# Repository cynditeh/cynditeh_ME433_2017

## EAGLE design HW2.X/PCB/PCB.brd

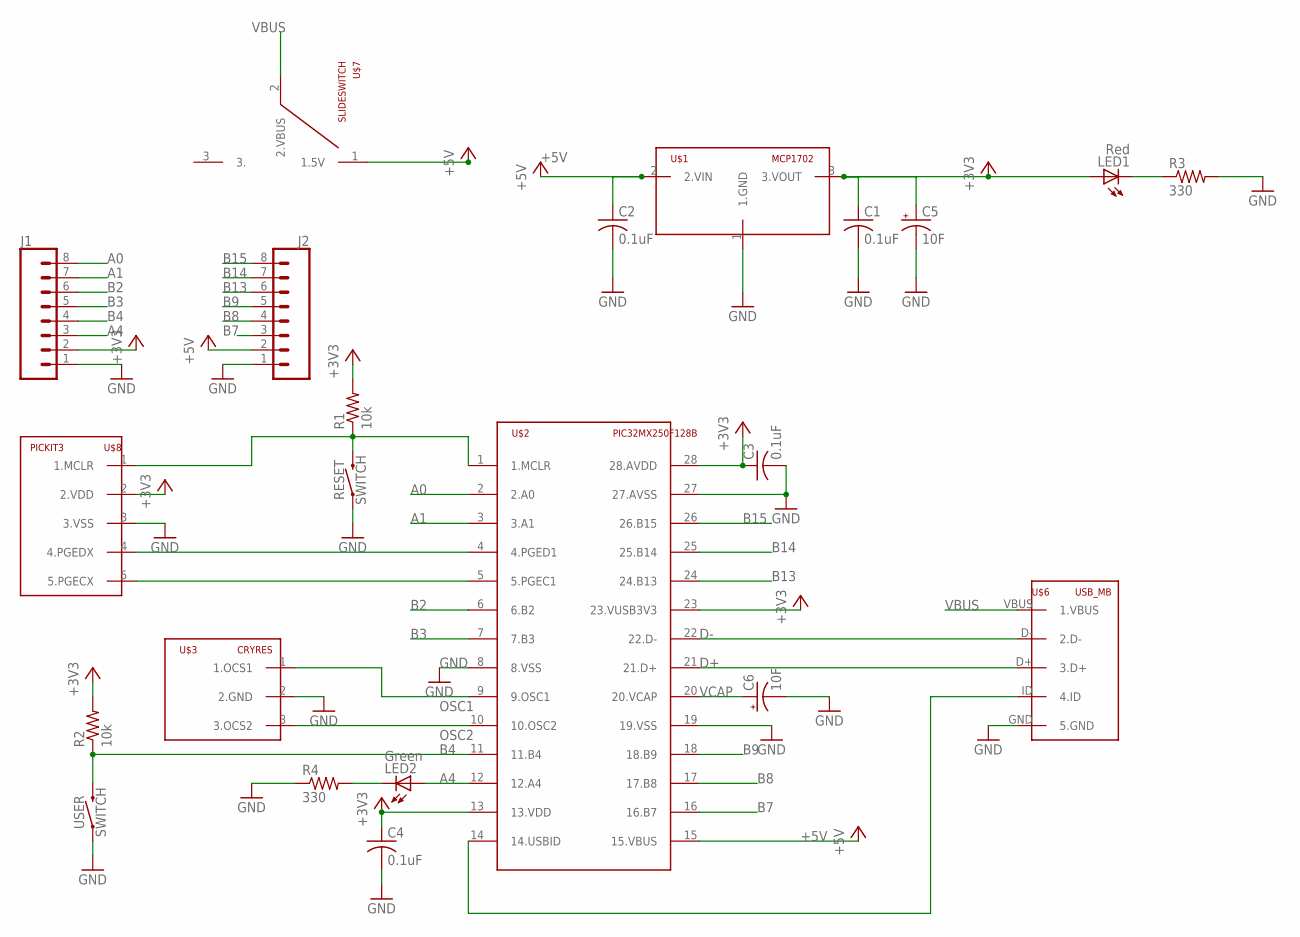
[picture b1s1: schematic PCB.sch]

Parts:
C1, C2, C3, C4: 0.1uF; C025-025X050
C5, C6: 10F; E5-5
J1, J2: CONN_08"; 1X08
LED1: Red; LED3MM
LED2: Green; LED3MM
R1, R2: 10k; 0207/10
R3, R4: 330; 0207/10
RESET: SWITCH
U$1: MCP1702; TO92
U$2: PIC32MX250F128B; DIL28-3
U$3: CRYRES; CRYSTAL
U$6: USB_MB; USB-MB-H
U$7: SLIDESWITCH
U$8: PICKIT3; 1X05
USER: SWITCH

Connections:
+3V3: C1.1, C3.1, C4.1, C5.+, J1.2, LED1.A, R1.2, R2.2, U$1.3 (3.VOUT), U$2.13 (13.VDD), U$2.23 (23.VUSB3V3), U$2.28 (28.AVDD), U$8.2 (2.VDD)
+5V: C2.1, J2.2, U$1.2 (2.VIN), U$2.15 (15.VBUS), U$7.1 (1.5V)
A0: J1.8, U$2.2 (2.A0)
A1: J1.7, U$2.3 (3.A1)
A4: J1.3, LED2.A, U$2.12 (12.A4)
B2: J1.6, U$2.6 (6.B2)
B3: J1.5, U$2.7 (7.B3)
B4: J1.4, R2.1, U$2.11 (11.B4), USER.2
B7: J2.3, U$2.16 (16.B7)
B8: J2.4, U$2.17 (17.B8)
B9: J2.5, U$2.18 (18.B9)
B13: J2.6, U$2.24 (24.B13)
B14: J2.7, U$2.25 (25.B14)
B15: J2.8, U$2.26 (26.B15)
D+: U$2.21 (21.D+), U$6.D+ (3.D+)
D-: U$2.22 (22.D-), U$6.D- (2.D-)
GND: C1.2, C2.2, C3.2, C4.2, C5.-, C6.-, J1.1, J2.1, R3.2, R4.1, RESET.1, U$1.1 (1.GND), U$2.8 (8.VSS), U$2.19 (19.VSS), U$2.27 (27.AVSS), U$3.2 (2.GND), U$6.GND (5.GND), U$8.3 (3.VSS), USER.1
MCLR: R1.1, RESET.2, U$2.1 (1.MCLR), U$8.1 (1.MCLR)
unnamed: LED1.K (C), R3.1
unnamed: LED2.K (C), R4.2
OSC1: U$2.9 (9.OSC1), U$3.1 (1.OCS1)
OSC2: U$2.10 (10.OSC2), U$3.3 (3.OCS2)
PEGC1: U$2.5 (5.PGEC1), U$8.5 (5.PGECX)
PEGD1: U$2.4 (4.PGED1), U$8.4 (4.PGEDX)
USBID: U$2.14 (14.USBID), U$6.ID (4.ID)
VBUS: U$6.VBUS (1.VBUS), U$7.2 (2.VBUS)
VCAP: C6.+, U$2.20 (20.VCAP)

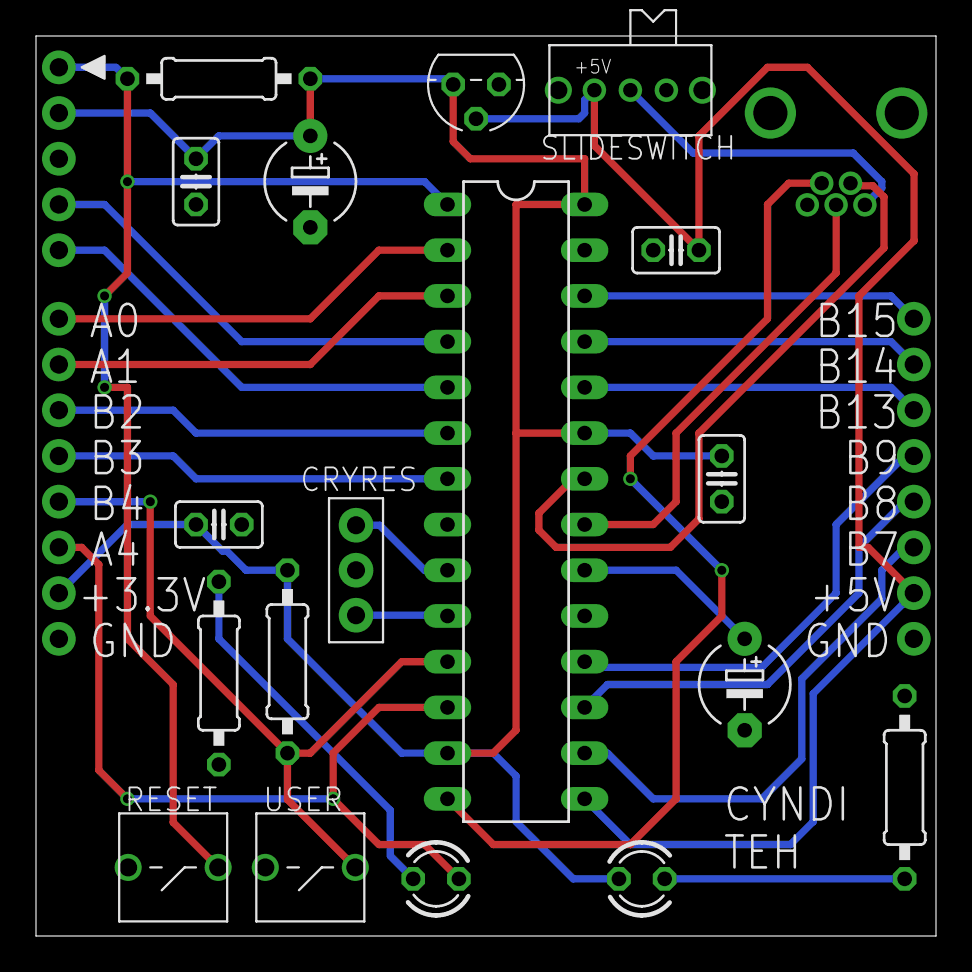
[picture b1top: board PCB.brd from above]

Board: 2 copper layers, 50.0 x 50.0 mm, 22 parts (0 on the bottom side), 27 nets.

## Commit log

2017-03-28 :circus_tent: Added .gitattributes
2017-03-28 Hello World!
2017-03-28 New change
2017-03-28 Added HW1 Project Folder
2017-03-29 Pragma config values
2017-03-29 Insert code to toggle LED
2017-03-29 HW1 7 part 3
2017-03-29 Implement 1000Hz blinking of LED
2017-03-29 Implement switch
2017-03-29 Edits to switch
2017-03-29 HW1 Pictures
2017-03-31 PCB Schematic
2017-03-31 PCB Schematics
2017-04-03 Update schematics
2017-04-04 PCB board arrangement of components
2017-04-04 Board update
2017-04-04 PCB Fix component positions
2017-04-05 PCB Update
2017-04-05 PCB Update with Labels
2017-04-05 Upload dru file
2017-04-06 Save Bitmap file
2017-04-06 Add bitmap
2017-04-06 Gerber files
2017-04-06 Create HW3 Files
2017-04-09 HW4 code initialization of SPI
2017-04-09 Code functions
2017-04-10 Make waveform
2017-04-10 Add image of waveform
2017-04-10 Add circuit diagram
2017-04-11 Update code
2017-04-12 Edit main and header
2017-04-12 Edit functions
2017-04-12 Edit i2c initialisation function
2017-04-13 Control LED with button function
2017-04-13 Finish up HW5
2017-04-15 Start HW6 code
2017-04-15 Clear screen to orange
2017-04-15 display_char function
2017-04-15 Implement progress bar
2017-04-18 Update HW6
2017-04-19 Create HW7 File
2017-04-19 Initialise IMU
2017-04-20 Read accelerometer and print values
2017-04-20 HW7 update
2017-04-20 Create HW8
2017-04-20 Harmony for HW1
2017-04-21 HW8 I2C
2017-04-26 HW9 Initialisatin
2017-04-26 HW9 Initialisation
2017-04-27 HW9 Implement IMU
2017-04-27 Update HW9
2017-04-27 HW9 Update
2017-04-28 Initialise HW10
2017-04-28 Code filters
2017-04-28 MATLAB Plot
2017-05-02 Plot graph in MATLAB
2017-05-04 Mouse movement
2017-05-08 HW12 Hello World
2017-05-11 HW13 with SeekBar
2017-05-16 HW14 CDC
2017-05-16 HW14 App button
2017-05-16 HW14 OTG Initial
2017-05-16 HW14 Send number back
2017-05-18 HW15 Wheel
2017-05-21 Box DXF
2017-05-23 HW16 and 17
2017-06-01 HW19 Tracker
2017-06-03 HW18 Control
2017-06-03 HW19 dot
2017-06-04 TechCup App
2017-06-04 Servo code
2017-06-09 RobotPics
